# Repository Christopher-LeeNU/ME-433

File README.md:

# ME-433

I don't know what I'm doing

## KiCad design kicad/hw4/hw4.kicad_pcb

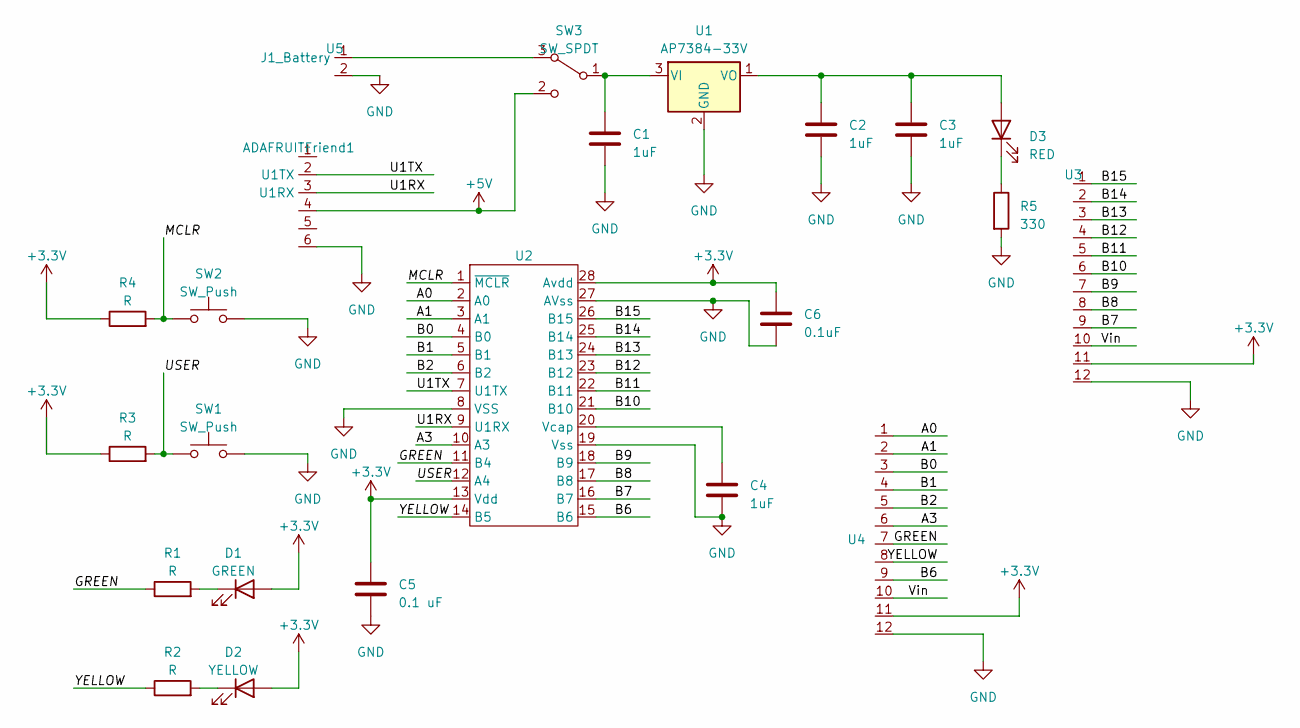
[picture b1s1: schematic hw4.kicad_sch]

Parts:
ADAFRUITFriend1: PinSocket_1x06_P2.54mm_Vertical
C1, C2, C3, C4: 1uF; C_Disc_D5.1mm_W3.2mm_P5.00mm
C5: 0.1 uF; C_Disc_D3.4mm_W2.1mm_P2.50mm
C6: 0.1uF; C_Disc_D3.4mm_W2.1mm_P2.50mm
D1: GREEN; LED_D3.0mm
D2: YELLOW; LED_D3.0mm
D3: RED; LED_D3.0mm
R1, R2, R3, R4: R; R_Axial_DIN0207_L6.3mm_D2.5mm_P7.62mm_Horizontal
R5: 330; R_Axial_DIN0207_L6.3mm_D2.5mm_P7.62mm_Horizontal
SW1, SW2: SW_Push; pb
SW3: SW_SPDT; slidesw2
U1: AP7384-33V; TO-92L_Inline
U2: DIP-28_W7.62mm_Socket
U3, U4: PinSocket_1x12_P2.54mm_Vertical
U5: PinSocket_1x02_P2.54mm_Vertical

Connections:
+3.3V: C5.1, C6.1, D1.2 (A), D2.2 (A), R3.1, R4.1, U2.13 (Vdd), U2.28 (Avdd), U3.11, U4.11
+5V: ADAFRUITFriend1.4, SW3.2 (C)
/A0: U2.2 (A0), U4.1
/A1: U2.3 (A1), U4.2
/A3: U2.10 (A3), U4.6
/B0: U2.4 (B0), U4.3
/B1: U2.5 (B1), U4.4
/B2: U2.6 (B2), U4.5
/B6: U2.15 (B6), U4.9
/B7: U2.16 (B7), U3.9
/B8: U2.17 (B8), U3.8
/B9: U2.18 (B9), U3.7
/B10: U2.21 (B10), U3.6
/B11: U2.22 (B11), U3.5
/B12: U2.23 (B12), U3.4
/B13: U2.24 (B13), U3.3
/B14: U2.25 (B14), U3.2
/B15: U2.26 (B15), U3.1
/GREEN: R1.1, U2.11 (B4), U4.7
/MCLR: R4.2, SW2.1, U2.1 (~MCLR)
/U1RX: ADAFRUITFriend1.3 (U1RX), U2.9 (U1RX)
/U1TX: ADAFRUITFriend1.2 (U1TX), U2.7 (U1TX)
/USER: R3.2, SW1.1, U2.12 (A4)
/Vin: U3.10, U4.10
/YELLOW: R2.1, U2.14 (B5), U4.8
GND: ADAFRUITFriend1.6, C1.2, C2.2, C3.2, C4.2, C5.2, C6.2, R5.2, SW1.2, SW2.2, U1.2 (GND), U2.8 (VSS), U2.19 (Vss), U2.27 (AVss), U3.12, U4.12, U5.2
unnamed: D1.1 (K), R1.2
unnamed: D2.1 (K), R2.2
unnamed: C2.1, C3.1, D3.2 (A), U1.1 (VO)
unnamed: D3.1 (K), R5.1
unnamed: SW3.3 (A), U5.1 (J1_Battery)
unnamed: C1.1, SW3.1 (B), U1.3 (VI)
unnamed: C4.1, U2.20 (Vcap)

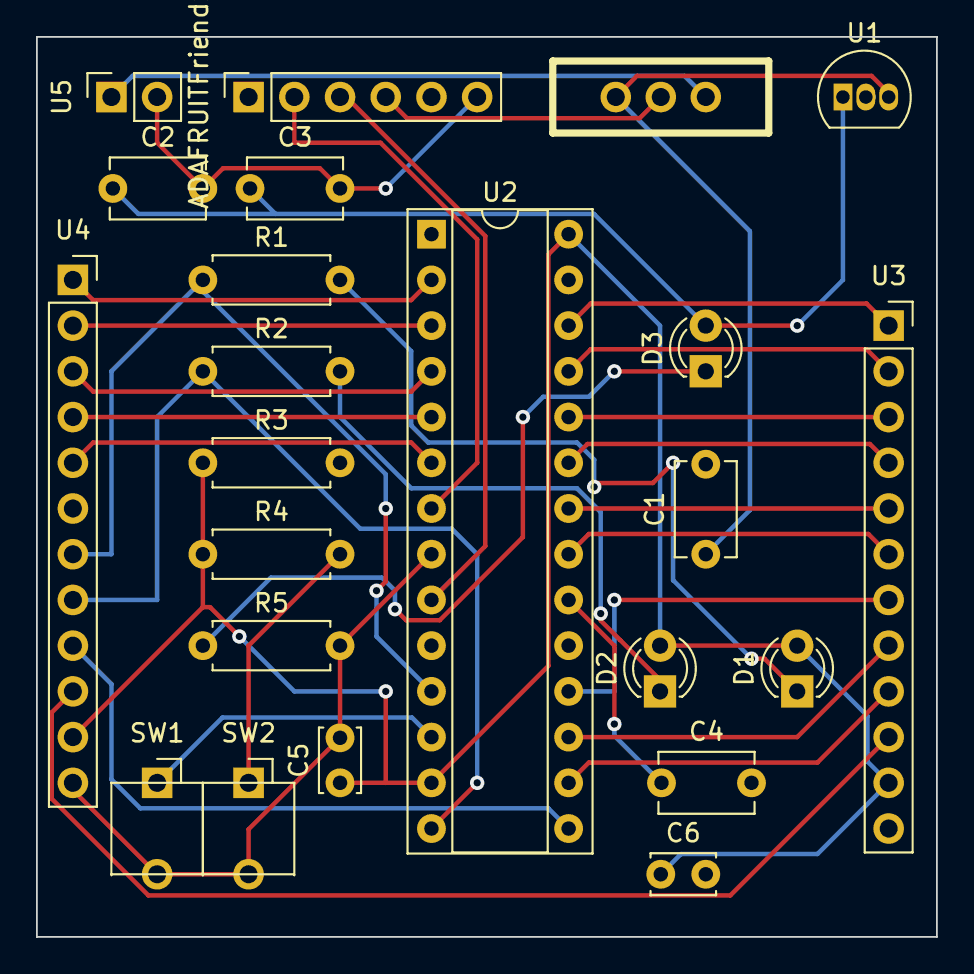
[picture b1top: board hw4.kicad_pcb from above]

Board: 2 copper layers, 50.0 x 50.0 mm, 23 parts (0 on the bottom side), 33 nets.

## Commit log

2023-04-11 I figured out how to use this thing
    yay
2023-04-23 New kicad files
2023-04-25 added picture
2023-04-25 fixed adding the picture
2023-05-02 hw6 stuff
2023-05-11 more hw7
2023-05-19 hw 10
2023-05-26 hw14
2023-05-27 hw11
2023-06-07 hw13
